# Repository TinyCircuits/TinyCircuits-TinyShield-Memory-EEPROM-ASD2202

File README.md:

# TinyCircuits TinyShield EEPROM / Flash / SRAM Memory Board
## ASD2202 Rev3

The design files are located under design_files/ for the TinyCircuits ASD2202 Rev 3 PCB.  This is a TinyShield board (20mm x 20mm) that has options for several different memory ICs.

Format is in Cadsoft Eagle format - Eagle version 6.2 was used for the original design.

For more infomation on this, check out the product page at TinyCircuits.com:  https://tinycircuits.com/products/eeprom-tinyshield

# License:

Design by TinyCircuits.
All design files are released under the Creative Commons Attribution Share-Alike 3.0 License, see the following link for details: http://creativecommons.org/licenses/by-sa/3.0

All text above must be included in any redistribution or derived design

This project uses designs and concepts developed as part of the Arduino project and the LilyPad project.  The TinyCircuits design files themselves (schematics, PCB and libraries) are not directly derived from these works' design files and have been created new, however the concepts and basic architecture behind the TinyDuino and TinyLily products are derived and we thank the hard work of the organizations below for their contributions to open-source hardware:
  
Original Arduino Uno Design by Team Arduino

LilyPad Arduino Design by Leah Buechley and Sparkfun Electronics

Please support the open-source hardware community

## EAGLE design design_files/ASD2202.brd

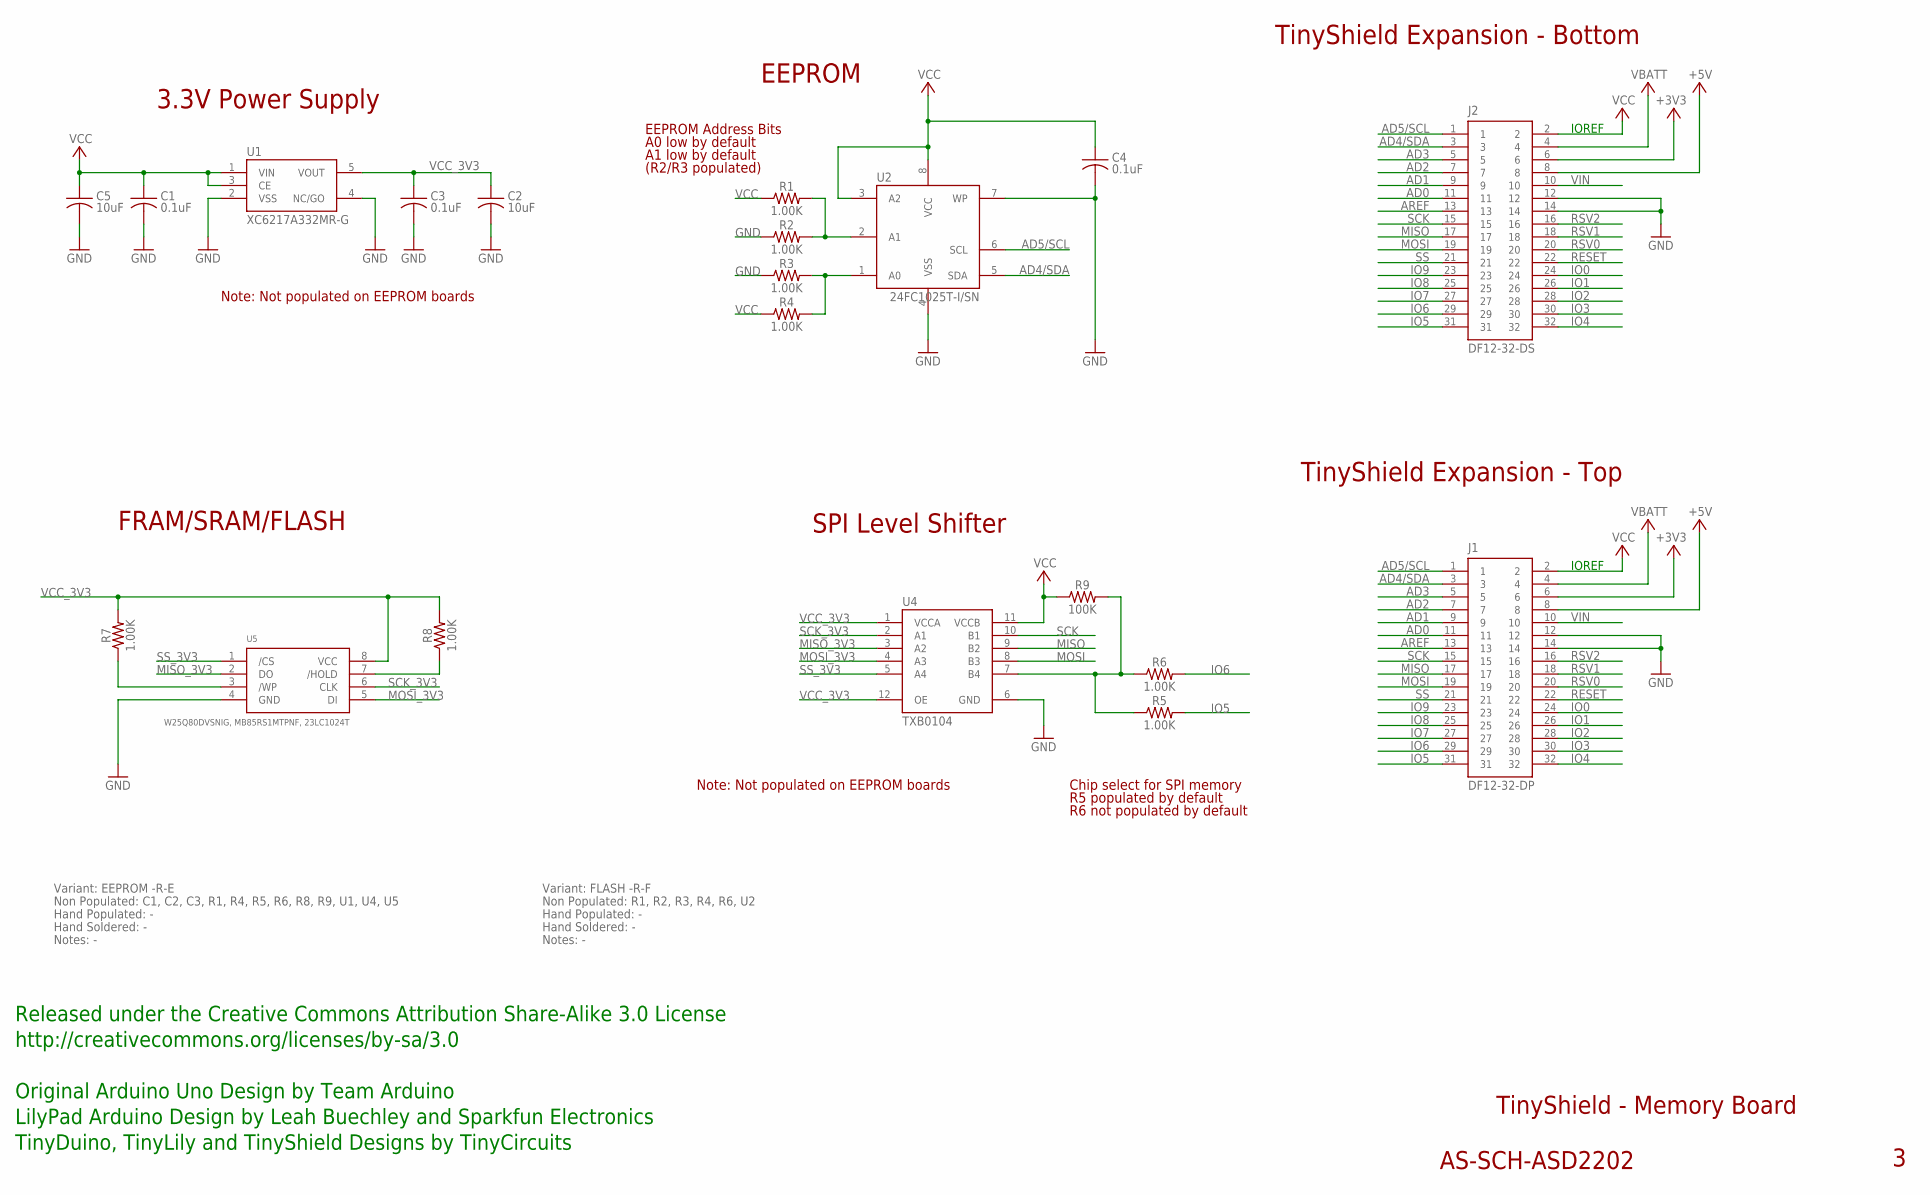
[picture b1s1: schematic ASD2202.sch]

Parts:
C1, C3, C4: 0.1uF; C0402; PARTNO AS-ITM-00008
C2: 10uF; C0805; PARTNO AS-ITM-00045
C5: 10uF; C0805
J1: DF12-32-DP; PARTNO AS-ITM-00015
J2: DF12-32-DS; PARTNO AS-ITM-00012
R1, R2, R3, R4, R5, R6: 1.00K; 0402; PARTNO AS-ITM-00003
R7, R8: 1.00K; 0402
R9: 100K; 0402; PARTNO AS-ITM-00004
U1: XC6217A332MR-G; SOT-25; PARTNO AS-ITM-00249
U2: 24FC1025T-I/SN; 8-SOIC-N
U4: TXB0104; UQFN-12
U5: W25Q80DVSNIG, MB85RS1MTPNF, 23LC1024T; 8-SOIC-N

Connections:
+3V3: J1.6, J2.6
+5V: J1.8, J2.8
AD0: J1.11, J2.11
AD1: J1.9, J2.9
AD2: J1.7, J2.7
AD3: J1.5, J2.5
AD4/SDA: J1.3, J2.3, U2.5 (SDA)
AD5/SCL: J1.1, J2.1, U2.6 (SCL)
AREF: J1.13, J2.13
GND: C1.2, C2.2, C3.2, C4.2, C5.2, J1.12, J1.14, J2.12, J2.14, R2.1, R3.1, U1.2 (VSS), U1.4 (NC/GO), U2.4 (VSS), U2.7 (WP), U4.6 (GND), U5.4 (GND)
IO0: J1.24, J2.24
IO1: J1.26, J2.26
IO2: J1.28, J2.28
IO3: J1.30, J2.30
IO4: J1.32, J2.32
IO5: J1.31, J2.31, R5.2
IO6: J1.29, J2.29, R6.2
IO7: J1.27, J2.27
IO8: J1.25, J2.25
IO9: J1.23, J2.23
MISO: J1.17, J2.17, U4.9 (B2)
MISO_3V3: U4.3 (A2), U5.2 (DO)
MOSI: J1.19, J2.19, U4.8 (B3)
MOSI_3V3: U4.4 (A3), U5.5 (DI)
unnamed: R8.1, U5.7 (/HOLD)
unnamed: R7.1, U5.3 (/WP)
unnamed: R1.2, R2.2, U2.2 (A1)
unnamed: R3.2, R4.2, U2.1 (A0)
unnamed: R5.1, R6.1, R9.2, U4.7 (B4)
RESET: J1.22, J2.22
RSV0: J1.20, J2.20
RSV1: J1.18, J2.18
RSV2: J1.16, J2.16
SCK: J1.15, J2.15, U4.10 (B1)
SCK_3V3: U4.2 (A1), U5.6 (CLK)
SS: J1.21, J2.21
SS_3V3: U4.5 (A4), U5.1 (/CS)
VBATT: J1.4, J2.4
VCC: C1.1, C4.1, C5.1, J1.2, J2.2, R1.1, R4.1, R9.1, U1.1 (VIN), U1.3 (CE), U2.3 (A2), U2.8 (VCC), U4.11 (VCCB)
VCC_3V3: C2.1, C3.1, R7.2, R8.2, U1.5 (VOUT), U4.1 (VCCA), U4.12 (OE), U5.8 (VCC)
VIN: J1.10, J2.10

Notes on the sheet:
TinyShield Expansion - Bottom
TinyShield - Memory Board
AS-SCH-ASD2202
TinyShield Expansion - Top
IOREF
Released under the Creative Commons Attribution Share-Alike 3.0 License
http://creativecommons.org/licenses/by-sa/3.0
LilyPad Arduino Design by Leah Buechley and Sparkfun Electronics
TinyDuino, TinyLily and TinyShield Designs by TinyCircuits
Original Arduino Uno Design by Team Arduino
EEPROM
3.3V Power Supply
SPI Level Shifter
FRAM/SRAM/FLASH
Chip select for SPI memory
R5 populated by default
R6 not populated by default
EEPROM Address Bits
A0 low by default
A1 low by default
(R2/R3 populated)
Note: Not populated on EEPROM boards
Non Populated: C1, C2, C3, R1, R4, R5, R6, R8, R9, U1, U4, U5
Hand Populated: -
Hand Soldered: -
Variant: EEPROM -R-E
Notes: -
Non Populated: R1, R2, R3, R4, R6, U2
Variant: FLASH -R-F

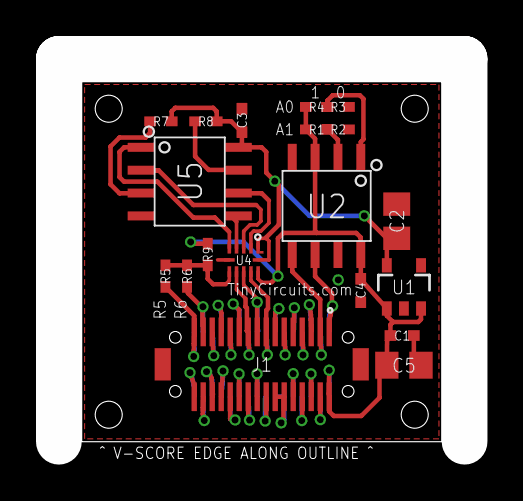
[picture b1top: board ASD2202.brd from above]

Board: 2 copper layers, 20.0 x 20.0 mm, 21 parts (1 on the bottom side), 41 nets.

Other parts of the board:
U$1: DOCFIELD-TINYCIRCUITS-PCB

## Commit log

2016-05-03 :tada: Added .gitattributes & .gitignore files
2017-06-08 Adding example sketch
    Adding the example sketch from the Flash Memory TinyShield, was
    previously located in a seperate repository.
2018-07-02 Added SRAM library
2019-01-04 update format
2019-01-07 resolved compatibility for TinyZero, updated comments
2019-01-07 resolved compatibility with SPIFlash update
2019-01-09 updated comments
2019-01-11 added tutorial images
2019-01-11 added serial monitor image
2019-01-11 added .zip files
2019-01-11 transferred old images
2019-01-11 updated images
2019-05-10 update pictures
2019-05-15 add flash shield pics
2019-05-22 added images and updated naming convention
2019-05-24 fix el eeprom:
2019-05-24 better wiki
2020-01-10 fix typo
2020-02-11 image update
2020-02-24 add FRAM
2020-07-28 Add CAD data
2020-08-14 Update CAD drawing
2021-09-09 Fixed off by one error
    If the page and offset were both 0, it would try to write to address -255. This pull request fixes this problem, the .zip is also updated.
